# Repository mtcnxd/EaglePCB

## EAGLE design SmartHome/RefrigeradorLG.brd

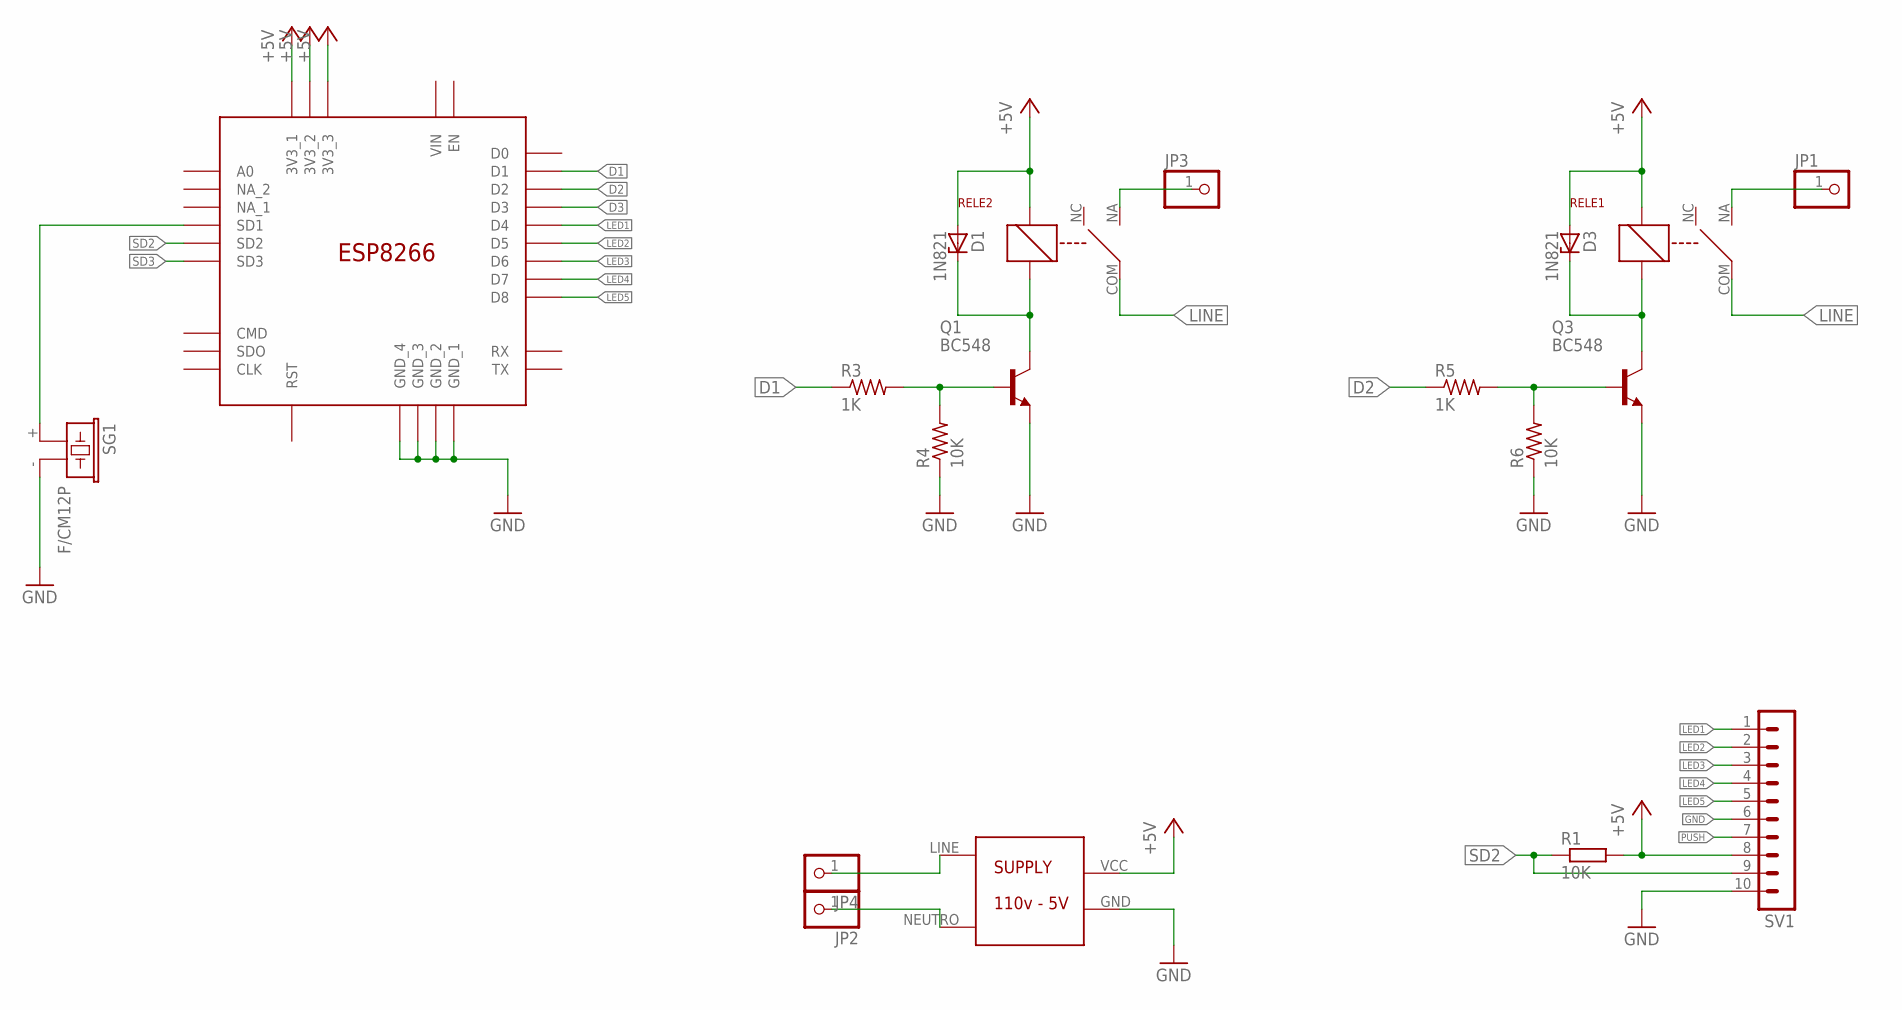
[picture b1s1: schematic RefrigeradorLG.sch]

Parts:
D1, D3: 1N821; DO35Z10
ESP8266: ESP8266
JP1, JP2, JP3, JP4: PINHD-1X1; 1X01
Q1, Q3: BC548; TO92-EBC
R1, R4, R6: 10K; 0204/7
R3, R5: 1K; 0204/7
RELE1, RELE2: RAS0510
SG1: F/CM12P
SV1: MA10-1
U$1: SUPPLY5V

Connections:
+5V: D1.A, D3.A, ESP8266.3V3_1, ESP8266.3V3_2, ESP8266.3V3_3, R1.2, RELE1.B1, RELE2.B1, SV1.8, U$1.VCC
D1: ESP8266.D1, R3.1
D2: ESP8266.D2, R5.1
D3: ESP8266.D3
GND: ESP8266.GND_1, ESP8266.GND_2, ESP8266.GND_3, ESP8266.GND_4, Q1.E, Q3.E, R4.1, R6.1, SG1.- (2), SV1.6, SV1.10, U$1.GND
LED1: ESP8266.D4, SV1.1
LED2: ESP8266.D5, SV1.2
LED3: ESP8266.D6, SV1.3
LED4: ESP8266.D7, SV1.4
LED5: ESP8266.D8, SV1.5
LINE: JP4.1, RELE1.COM, RELE2.COM, U$1.LINE
unnamed: ESP8266.SD1, SG1.+ (1)
unnamed: JP2.1, U$1.NEUTRO
unnamed: Q1.B, R3.2, R4.2
unnamed: D1.C, Q1.C, RELE2.B2
unnamed: Q3.B, R5.2, R6.2
unnamed: D3.C, Q3.C, RELE1.B2
unnamed: JP3.1, RELE2.NA
unnamed: JP1.1, RELE1.NA
PUSH: SV1.7
SD2: ESP8266.SD2, R1.1, SV1.9
SD3: ESP8266.SD3

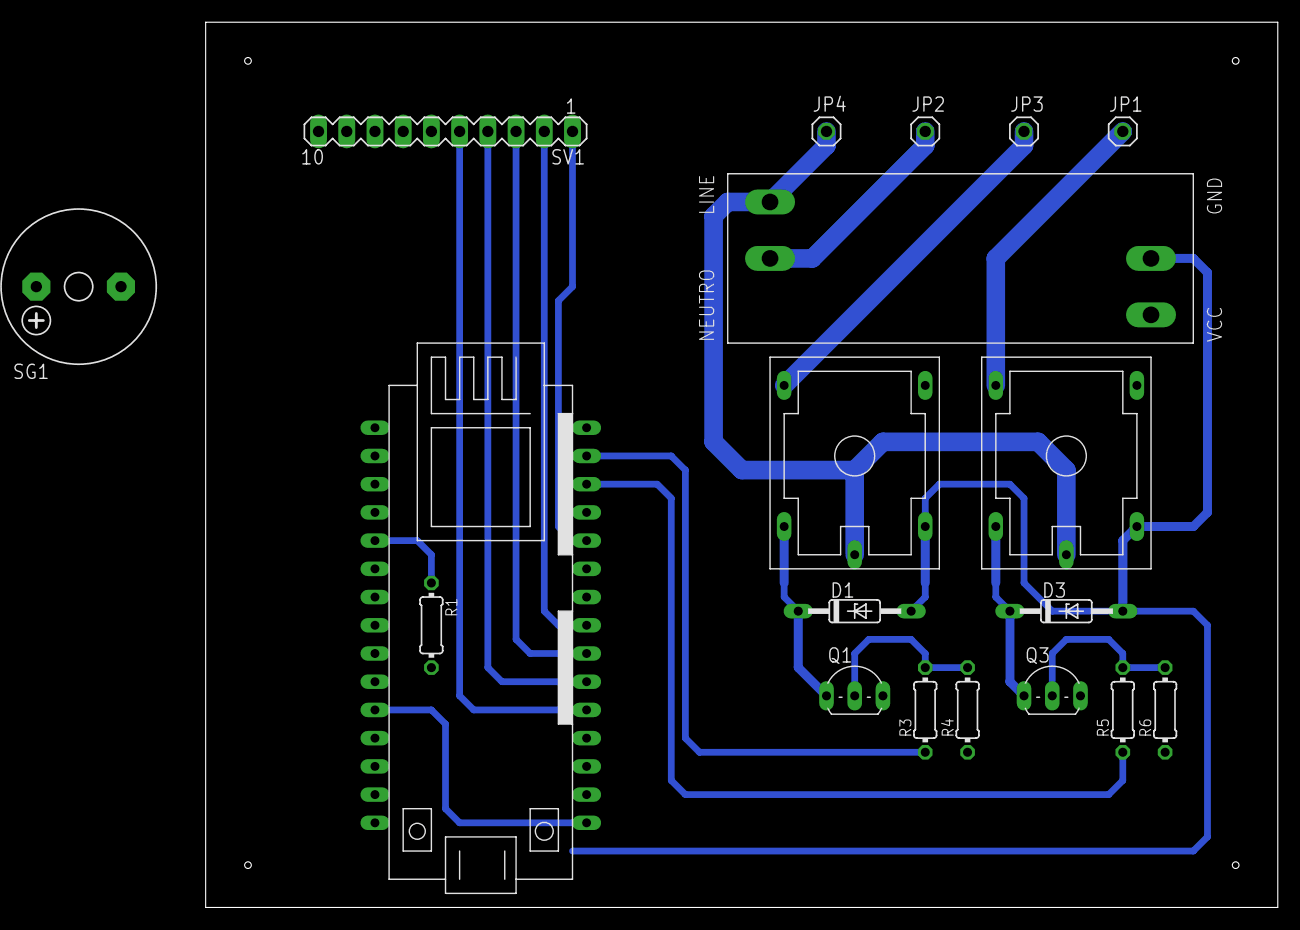
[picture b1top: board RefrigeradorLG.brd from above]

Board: 2 copper layers, 96.5 x 79.7 mm, 19 parts (0 on the bottom side), 19 nets.

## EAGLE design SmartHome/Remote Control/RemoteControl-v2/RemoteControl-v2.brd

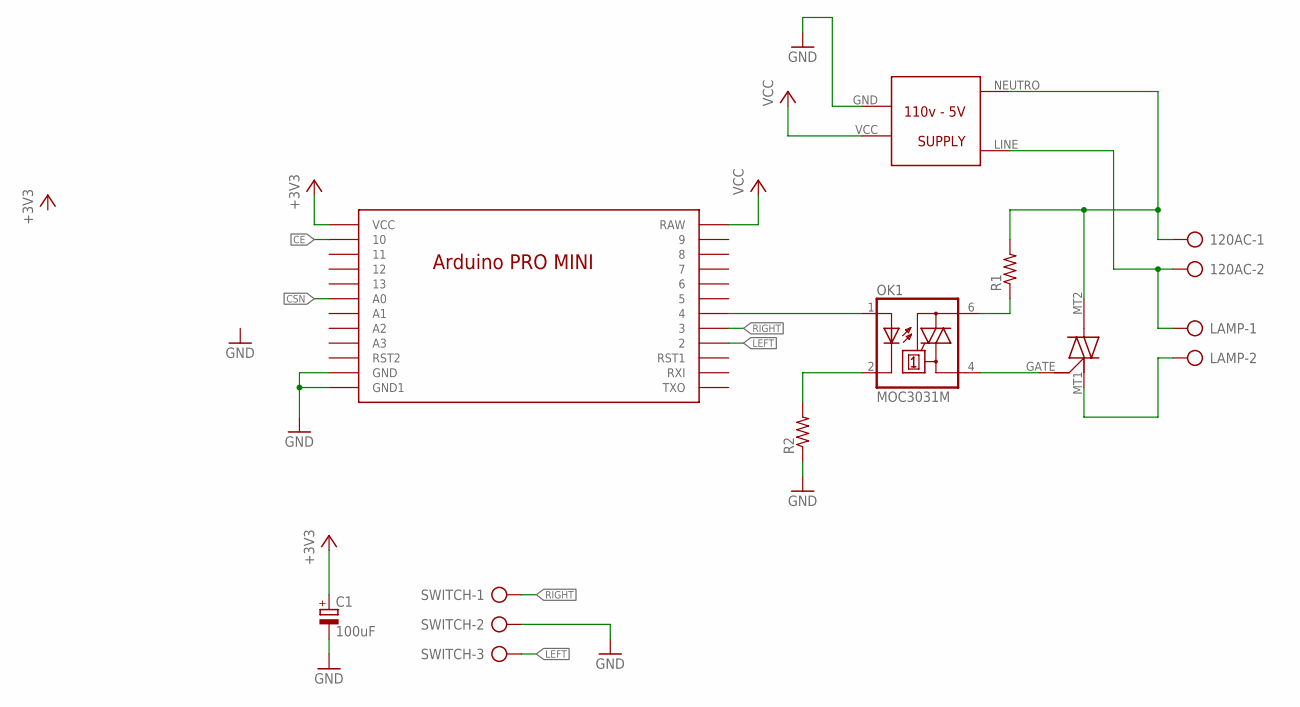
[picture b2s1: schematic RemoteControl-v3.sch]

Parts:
120AC: AK300/2
C1: 100uF; E2,5-5
LAMP: AK300/2
OK1: MOC3031M; DIL06
R1, R2: R-US_0204/7; 0204/7
SWITCH: AK300/3
U$1: NANO
U$2: MAC12
U$3: SUPPLY5V

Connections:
+3V3: C1.+, U$1.VCC; also elsewhere on the board
CE: U$1.10; also elsewhere on the board
CSN: U$1.A0; also elsewhere on the board
GND: C1.-, R2.1, SWITCH.2, U$1.GND1 (GND), U$1.GND2 (GND1), U$3.GND; also elsewhere on the board
LEFT: SWITCH.3, U$1.2
unnamed 5: U$1.13; also elsewhere on the board
unnamed 6: U$1.12; also elsewhere on the board
unnamed 7: U$1.11; also elsewhere on the board
unnamed: OK1.6 (A2), R1.1
unnamed: LAMP.2, U$2.MT1
unnamed: 120AC.2, LAMP.1, U$3.LINE
unnamed: 120AC.1, R1.2, U$2.MT2, U$3.NEUTRO
unnamed: OK1.2 (C), R2.2
unnamed: OK1.4 (A1), U$2.GATE
unnamed: OK1.1 (A), U$1.4
RIGHT: SWITCH.1, U$1.3
VCC: U$1.RAW, U$3.VCC

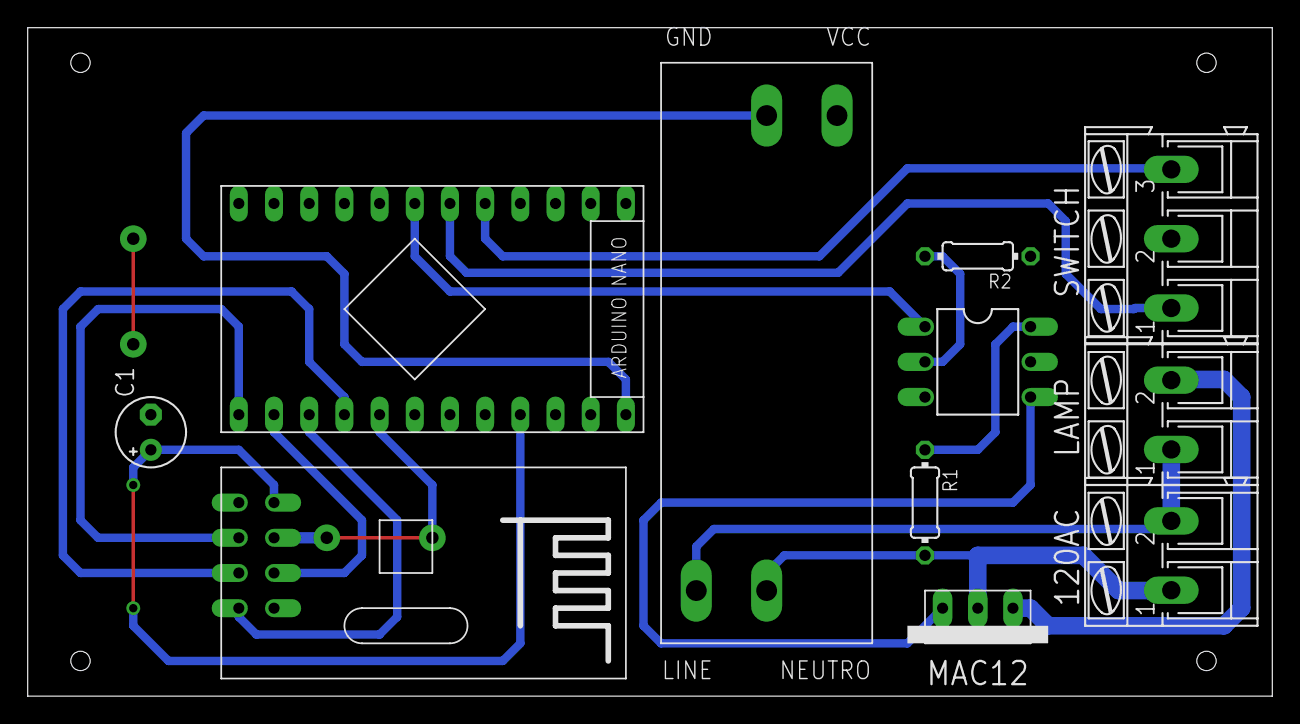
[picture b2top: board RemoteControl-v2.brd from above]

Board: 2 copper layers, 89.8 x 48.2 mm, 11 parts (0 on the bottom side), 17 nets.

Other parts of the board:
NRF24L01: NRF24L01

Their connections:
+3V3: NRF24L01.VDD; also elsewhere on the board
CE: NRF24L01.CE; also elsewhere on the board
CSN: NRF24L01.CSN; also elsewhere on the board
GND: NRF24L01.GND; also elsewhere on the board
unnamed 5: NRF24L01.SCK; also elsewhere on the board
unnamed 6: NRF24L01.MISO; also elsewhere on the board
unnamed 7: NRF24L01.MOSI; also elsewhere on the board

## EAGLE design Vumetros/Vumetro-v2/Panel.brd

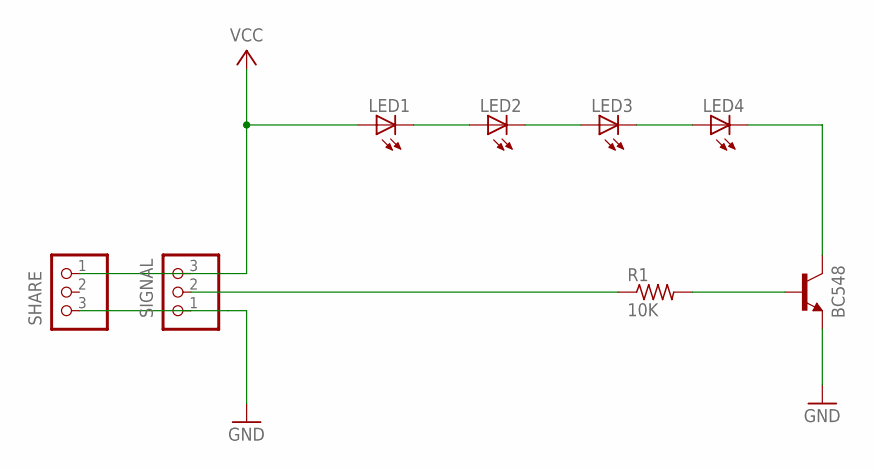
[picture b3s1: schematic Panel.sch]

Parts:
LED1, LED2, LED3, LED4: LED10MM
Q1: BC548; TO92-EBC
R1: 10K; 0204/7
SHARE: PINHD-1X3/90; 1X03/90
SIGNAL: PINHD-1X3/90; 1X03/90

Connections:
GND: Q1.E, SHARE.3, SIGNAL.1
unnamed: LED4.K (C), Q1.C
unnamed: Q1.B, R1.2
unnamed: LED1.K (C), LED2.A
unnamed: LED2.K (C), LED3.A
unnamed: LED3.K (C), LED4.A
unnamed: R1.1, SIGNAL.2
VCC: LED1.A, SHARE.1, SIGNAL.3

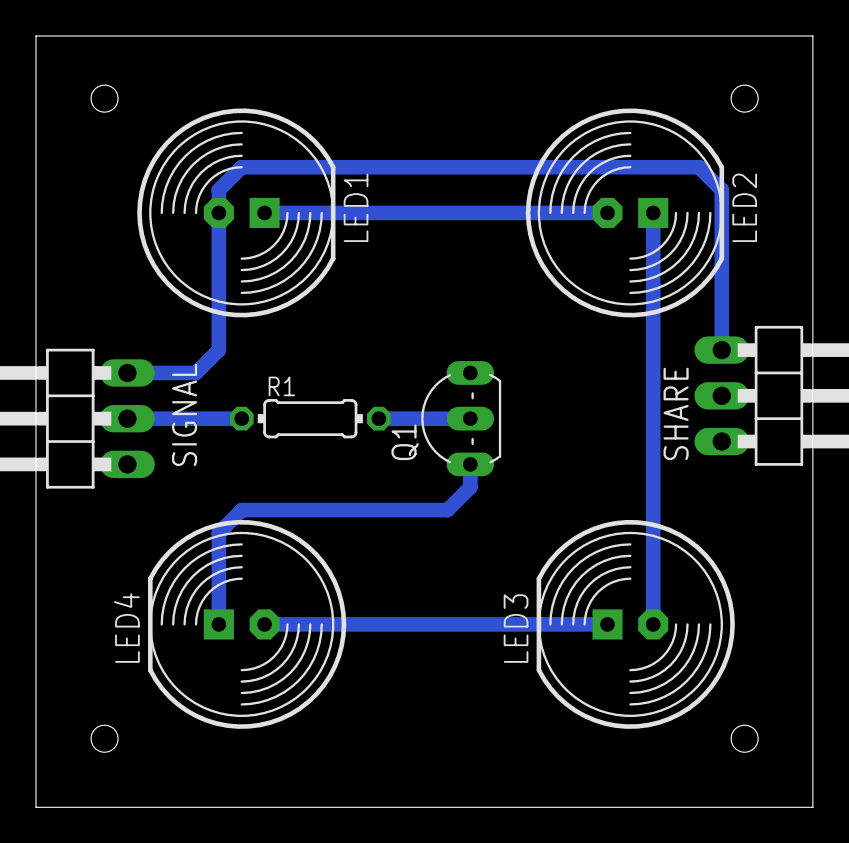
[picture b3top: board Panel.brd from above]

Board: 2 copper layers, 43.2 x 42.9 mm, 8 parts (0 on the bottom side), 8 nets.

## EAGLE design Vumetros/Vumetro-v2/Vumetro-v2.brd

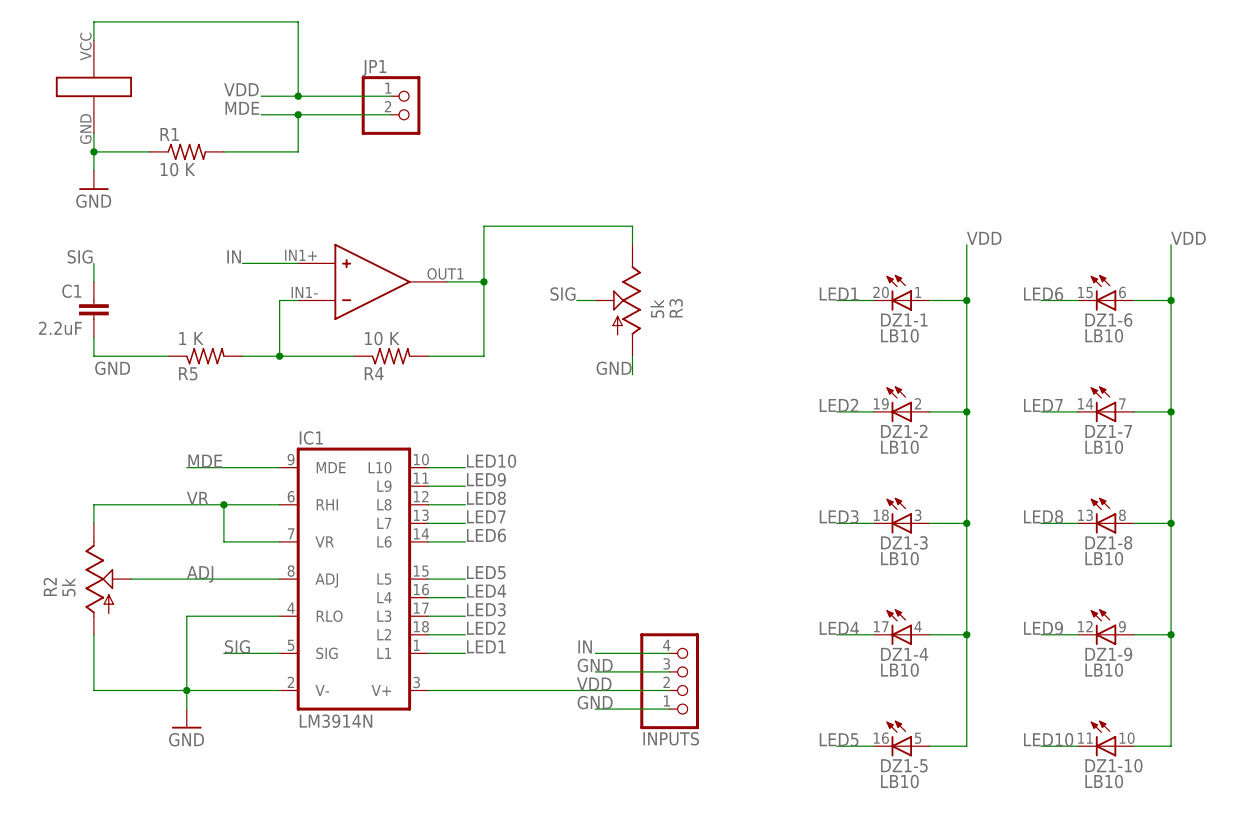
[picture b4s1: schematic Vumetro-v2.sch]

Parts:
C1: 2.2uF; C2.5-6
DZ1: LB10
IC1: LM3914N; DIL18
INPUTS: PINHD-1X4; 1X04
JP1: PINHD-1X2; 1X02
R1, R4: 10 K; 0204/5
R2, R3: 5k; PT-10
R5: 1 K; 0204/5
U$1: LM358

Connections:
ADJ: IC1.8 (ADJ), R2.S
GND: C1.2, IC1.2 (V-), IC1.4 (RLO), INPUTS.1, INPUTS.3, R1.1, R2.A, R3.A, R5.1, U$1.GND
IN: INPUTS.4, U$1.IN1+ (IN+)
LED1: DZ1.20 (C), IC1.1 (L1)
LED2: DZ1.19 (C), IC1.18 (L2)
LED3: DZ1.18 (C), IC1.17 (L3)
LED4: DZ1.17 (C), IC1.16 (L4)
LED5: DZ1.16 (C), IC1.15 (L5)
LED6: DZ1.15 (C), IC1.14 (L6)
LED7: DZ1.14 (C), IC1.13 (L7)
LED8: DZ1.13 (C), IC1.12 (L8)
LED9: DZ1.12 (C), IC1.11 (L9)
LED10: DZ1.11 (C), IC1.10 (L10)
MDE: IC1.9 (MDE), JP1.2, R1.2
unnamed: R4.1, R5.2, U$1.IN1- (IN-)
unnamed: R3.E, R4.2, U$1.OUT1 (OUT)
SIG: C1.1, IC1.5 (SIG), R3.S
VDD: DZ1.1 (A), DZ1.2 (A), DZ1.3 (A), DZ1.4 (A), DZ1.5 (A), DZ1.6 (A), DZ1.7 (A), DZ1.8 (A), DZ1.9 (A), DZ1.10 (A), IC1.3 (V+), INPUTS.2, JP1.1, U$1.VCC
VR: IC1.6 (RHI), IC1.7 (VR), R2.E

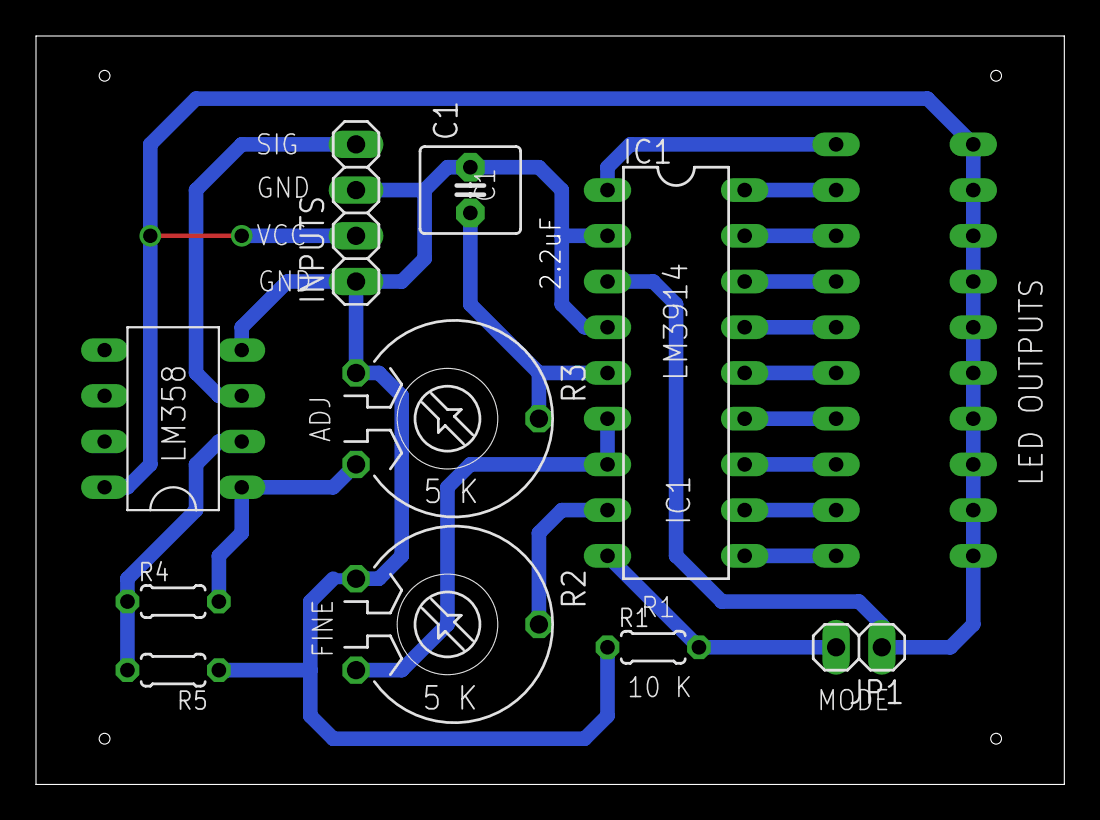
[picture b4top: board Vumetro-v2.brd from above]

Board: 2 copper layers, 57.1 x 41.6 mm, 11 parts (1 on the bottom side), 19 nets.
